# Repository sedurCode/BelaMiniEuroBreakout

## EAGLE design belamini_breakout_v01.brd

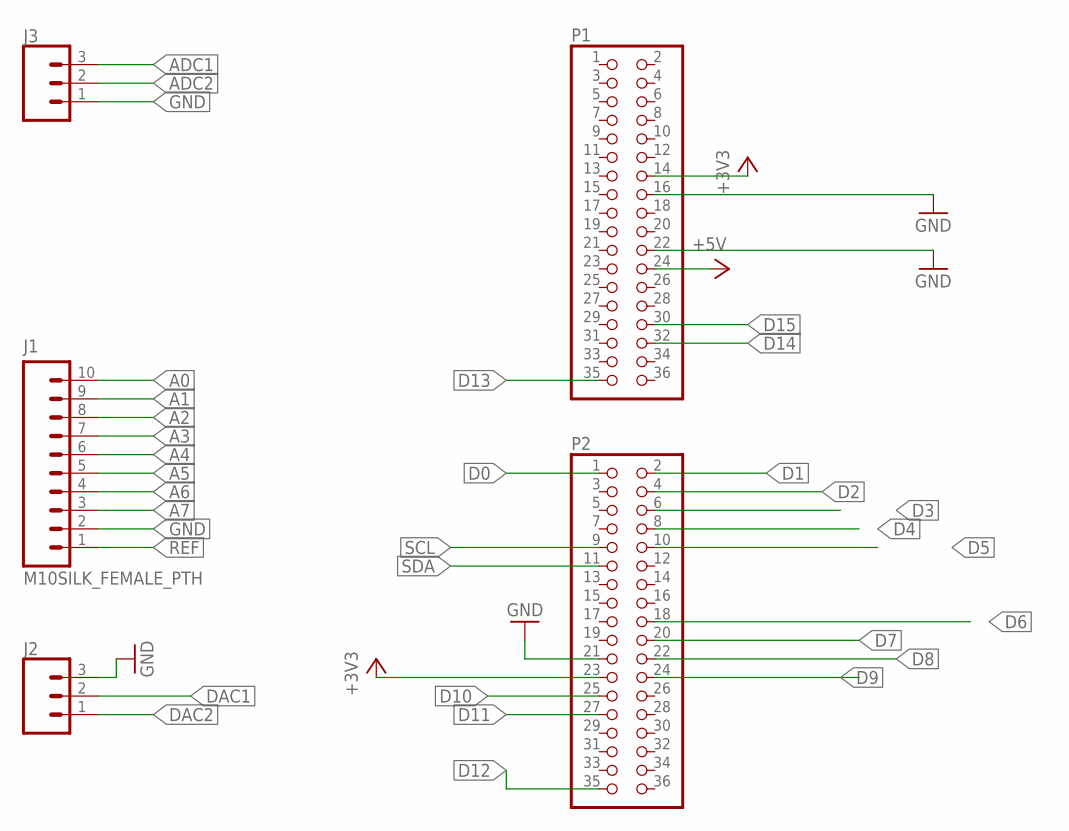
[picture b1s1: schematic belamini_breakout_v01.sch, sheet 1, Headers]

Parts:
J1: M10SILK_FEMALE_PTH; 1X10
J2, J3: CONN_03; 1X03
P1, P2: PINHD-2X18; 2X18

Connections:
+3V3: P1.14, P2.23; also elsewhere on the board
+5V: P1.24; also elsewhere on the board
A0: J1.10; also elsewhere on the board
A1: J1.9; also elsewhere on the board
A2: J1.8; also elsewhere on the board
A3: J1.7; also elsewhere on the board
A4: J1.6
A5: J1.5
A6: J1.4
A7: J1.3
ADC1: J3.3; also elsewhere on the board
ADC2: J3.2; also elsewhere on the board
D0: P2.1; also elsewhere on the board
D1: P2.2; also elsewhere on the board
D2: P2.4; also elsewhere on the board
D3: P2.6; also elsewhere on the board
D4: P2.8; also elsewhere on the board
D5: P2.10; also elsewhere on the board
D6: P2.18; also elsewhere on the board
D7: P2.20; also elsewhere on the board
D8: P2.22; also elsewhere on the board
D9: P2.24; also elsewhere on the board
D10: P2.25; also elsewhere on the board
D11: P2.27; also elsewhere on the board
D12: P2.35
D13: P1.35; also elsewhere on the board
D14: P1.32; also elsewhere on the board
D15: P1.30; also elsewhere on the board
DAC1: J2.2; also elsewhere on the board
DAC2: J2.1; also elsewhere on the board
GND: J1.2, J2.3, J3.1, P1.16, P1.22, P2.21; also elsewhere on the board
REF: J1.1
SCL: P2.9
SDA: P2.11

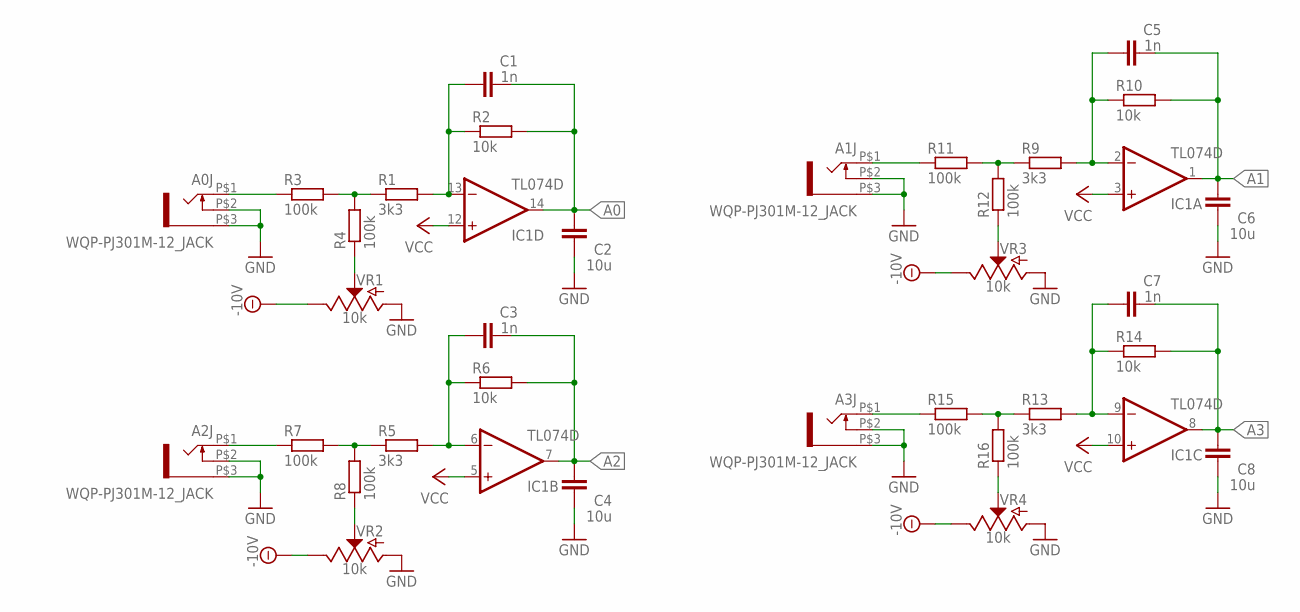
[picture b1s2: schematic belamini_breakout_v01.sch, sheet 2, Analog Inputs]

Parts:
A0J, A1J, A2J, A3J: WQP-PJ301M-12_JACK
C1, C3, C5, C7: 1n; C0603
C2, C4, C6, C8: 10u; C0603
IC1: TL074D; SO14
R1, R5, R9, R13: 3k3; R0603
R2, R6, R10, R14: 10k; R0603
R3, R4, R7, R8, R11, R12, R15, R16: 100k; R0603
VR1, VR2, VR3, VR4: 10k; POT-PTH-ALPS-KIT

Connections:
-10V: VR1.P$1 (E), VR2.P$1 (E), VR3.P$1 (E), VR4.P$1 (E); also elsewhere on the board
A0: C1.2, C2.2, IC1.14 (OUT), R2.2; also elsewhere on the board
A1: C5.2, C6.2, IC1.1 (OUT), R10.2; also elsewhere on the board
A2: C3.2, C4.2, IC1.7 (OUT), R6.2; also elsewhere on the board
A3: C7.2, C8.2, IC1.8 (OUT), R14.2; also elsewhere on the board
GND: A0J.P$2 (3), A0J.P$3 (1), A1J.P$2 (3), A1J.P$3 (1), A2J.P$2 (3), A2J.P$3 (1), A3J.P$2 (3), A3J.P$3 (1), C2.1, C4.1, C6.1, C8.1, VR1.P$3 (A), VR2.P$3 (A), VR3.P$3 (A), VR4.P$3 (A); also elsewhere on the board
unnamed: A0J.P$1 (2), R3.1
unnamed: C1.1, IC1.13 (-IN), R1.2, R2.1
unnamed: R1.1, R3.2, R4.2
unnamed: R4.1, VR1.P$2 (S)
unnamed: C3.1, IC1.6 (-IN), R5.2, R6.1
unnamed: R5.1, R7.2, R8.2
unnamed: A2J.P$1 (2), R7.1
unnamed: R8.1, VR2.P$2 (S)
unnamed: C5.1, IC1.2 (-IN), R9.2, R10.1
unnamed: R9.1, R11.2, R12.2
unnamed: A1J.P$1 (2), R11.1
unnamed: R12.1, VR3.P$2 (S)
unnamed: C7.1, IC1.9 (-IN), R13.2, R14.1
unnamed: R13.1, R15.2, R16.2
unnamed: A3J.P$1 (2), R15.1
unnamed: R16.1, VR4.P$2 (S)
VCC: IC1.3 (+IN), IC1.5 (+IN), IC1.10 (+IN), IC1.12 (+IN); also elsewhere on the board

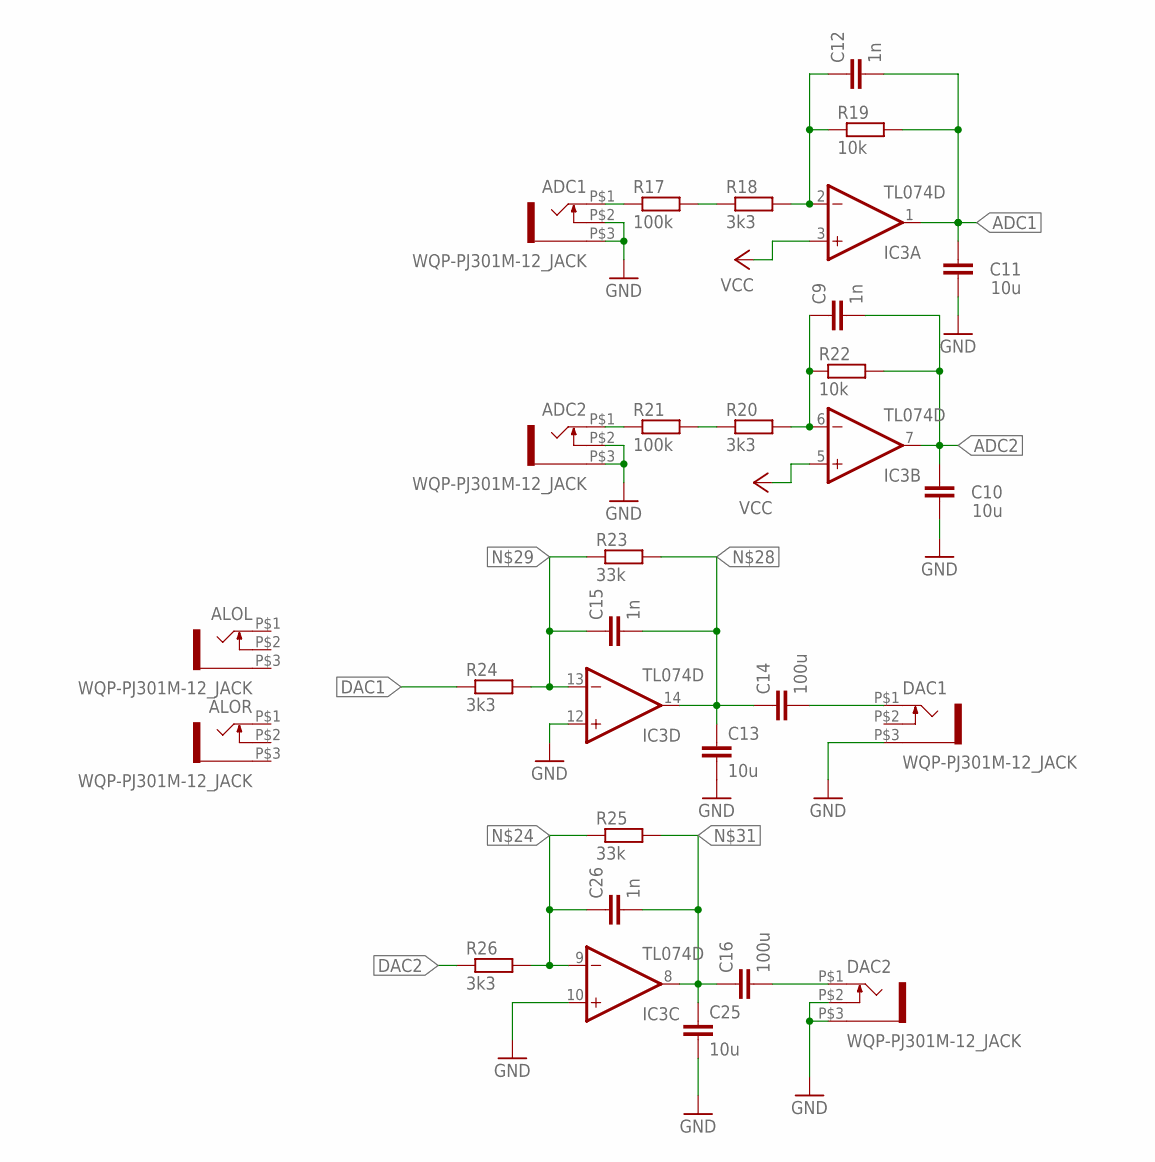
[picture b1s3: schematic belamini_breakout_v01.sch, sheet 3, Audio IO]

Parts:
ADC1, ADC2: WQP-PJ301M-12_JACK
ALOL: WQP-PJ301M-12_JACK
ALOR: WQP-PJ301M-12_JACK
C9, C12, C15, C26: 1n; C0603
C10, C11, C13, C25: 10u; C0603
C14, C16: 100u; C0603
DAC1, DAC2: WQP-PJ301M-12_JACK
IC3: TL074D; SO14
R17, R21: 100k; R0603
R18, R20, R24, R26: 3k3; R0603
R19, R22: 10k; R0603
R23, R25: 33k; R0603

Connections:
ADC1: C11.2, C12.2, IC3.1 (OUT), R19.2; also elsewhere on the board
ADC2: C9.2, C10.2, IC3.7 (OUT), R22.2; also elsewhere on the board
DAC1: R24.1; also elsewhere on the board
DAC2: R26.1; also elsewhere on the board
GND: ADC1.P$2 (3), ADC1.P$3 (1), ADC2.P$2 (3), ADC2.P$3 (1), C10.1, C11.1, C13.2, C25.2, DAC1.P$3 (1), DAC2.P$2 (3), DAC2.P$3 (1), IC3.10 (+IN), IC3.12 (+IN); also elsewhere on the board
unnamed: ADC1.P$1 (2), R17.1
unnamed: R17.2, R18.1
unnamed: C12.1, IC3.2 (-IN), R18.2, R19.1
unnamed: C9.1, IC3.6 (-IN), R20.2, R22.1
unnamed: C26.1, IC3.9 (-IN), R25.1, R26.2
unnamed: R20.1, R21.2
unnamed: ADC2.P$1 (2), R21.1
unnamed: C14.2, DAC1.P$1 (2)
unnamed: C13.1, C14.1, C15.2, IC3.14 (OUT), R23.2
unnamed: C15.1, IC3.13 (-IN), R23.1, R24.2
unnamed: C16.1, C25.1, C26.2, IC3.8 (OUT), R25.2
unnamed: C16.2, DAC2.P$1 (2)
VCC: IC3.3 (+IN), IC3.5 (+IN); also elsewhere on the board

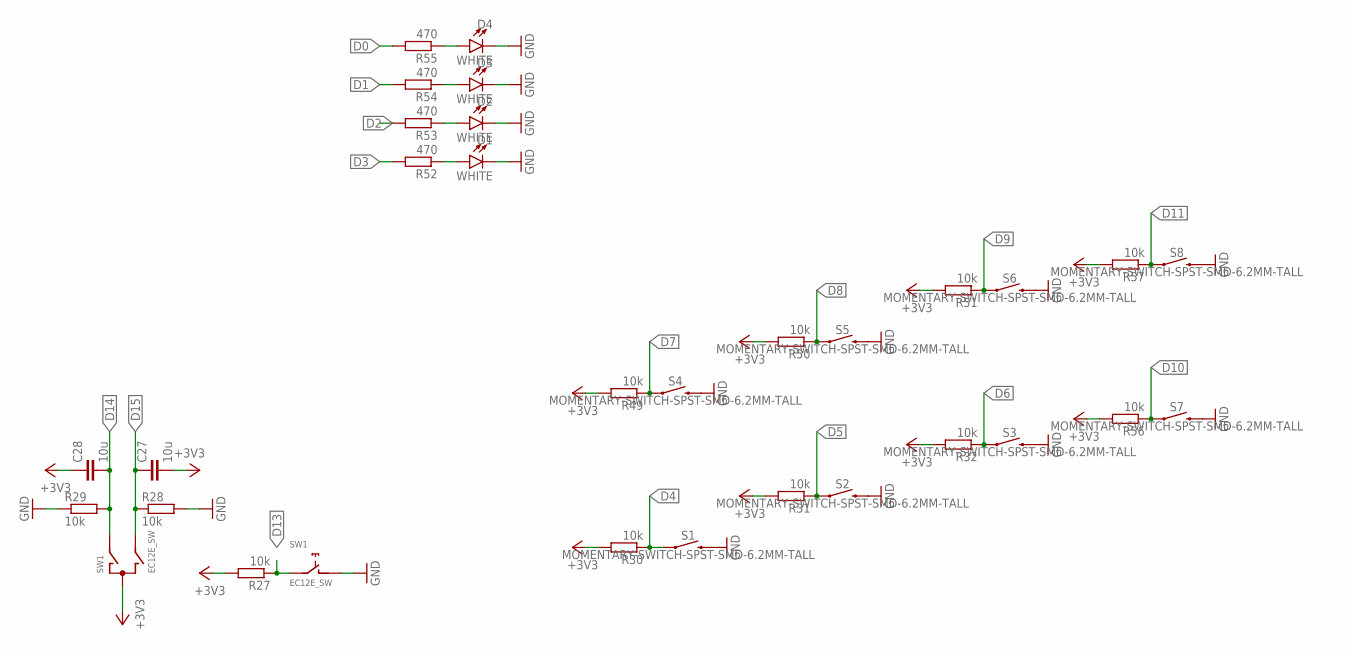
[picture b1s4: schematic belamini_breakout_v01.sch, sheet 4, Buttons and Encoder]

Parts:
C27, C28: 10u; C0603
D1, D2, D3, D4: WHITE; LED-1206
R27, R28, R29, R30, R31, R32, R49, R50, R51, R56, R57: 10k; R0603
R52, R53, R54, R55: 470; R0603
S1, S2, S3, S4, S5, S6, S7, S8: MOMENTARY-SWITCH-SPST-SMD-6.2MM-TALL; TACTILE_SWITCH_SMD_6.2MM_TALL
SW1: EC12E_SW; ALPS_EC12E_SW

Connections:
+3V3: C27.2, C28.1, R27.2, R30.2, R31.2, R32.2, R49.2, R50.2, R51.2, R56.2, R57.2, SW1.C; also elsewhere on the board
D0: R55.2; also elsewhere on the board
D1: R54.2; also elsewhere on the board
D2: R53.2; also elsewhere on the board
D3: R52.2; also elsewhere on the board
D4: R30.1, S1.A2 (1); also elsewhere on the board
D5: R31.1, S2.A2 (1); also elsewhere on the board
D6: R32.1, S3.A2 (1); also elsewhere on the board
D7: R49.1, S4.A2 (1); also elsewhere on the board
D8: R50.1, S5.A2 (1); also elsewhere on the board
D9: R51.1, S6.A2 (1); also elsewhere on the board
D10: R56.1, S7.A2 (1); also elsewhere on the board
D11: R57.1, S8.A2 (1); also elsewhere on the board
D13: R27.1, SW1.E (2); also elsewhere on the board
D14: C28.2, R29.2, SW1.A; also elsewhere on the board
D15: C27.1, R28.1, SW1.B; also elsewhere on the board
GND: D1.C, D2.C, D3.C, D4.C, R28.2, R29.1, S1.B2 (2), S2.B2 (2), S3.B2 (2), S4.B2 (2), S5.B2 (2), S6.B2 (2), S7.B2 (2), S8.B2 (2), SW1.D (1); also elsewhere on the board
unnamed: D4.A, R55.1
unnamed: D3.A, R54.1
unnamed: D2.A, R53.1
unnamed: D1.A, R52.1

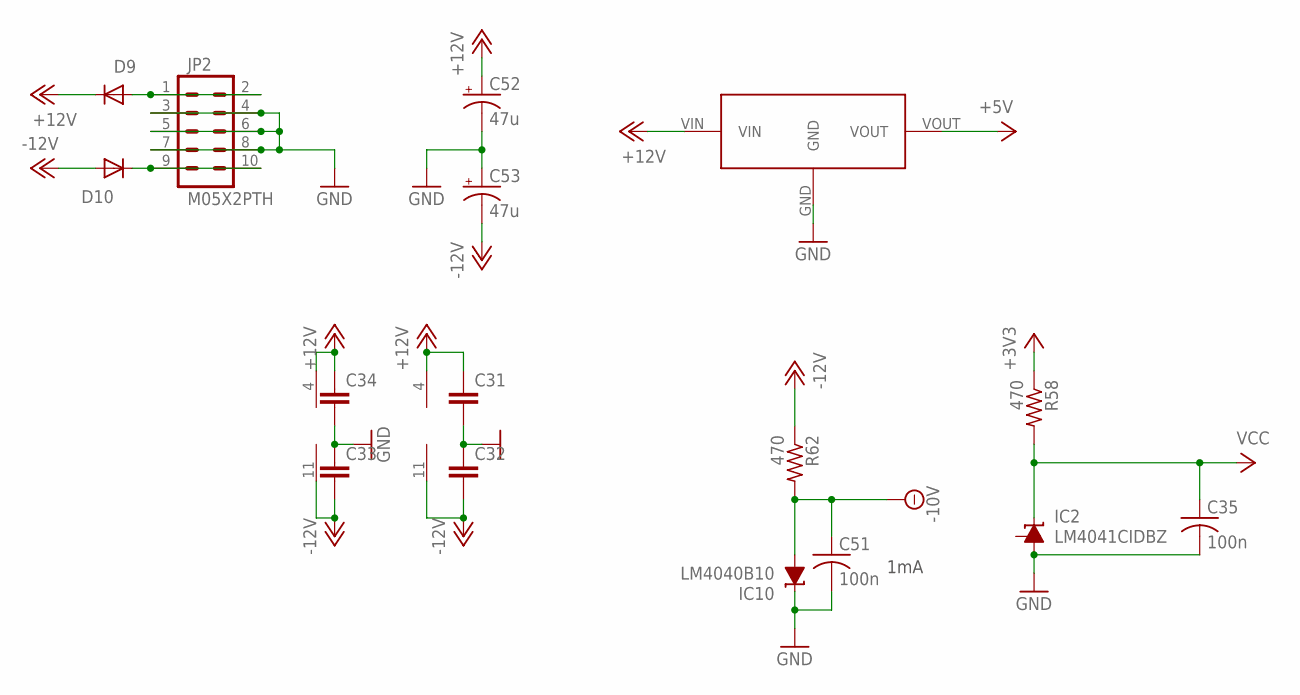
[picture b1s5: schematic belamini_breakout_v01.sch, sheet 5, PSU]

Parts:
C31, C32, C33, C34: C-EUC0603; C0603
C35, C51: 100n; C0603
C52, C53: 47u; PANASONIC_D
D9, D10: 1N5819HW; SOD123
IC1, IC3: TL074D; SO14
IC2: LM4041CIDBZ; DBZ_R-PDSO-G3
IC10: LM4040B10; DBZ_R-PDSO-G3
JP2: M05X2PTH; AVR_ICSP
R58, R62: 470; R0603
U$1: RECOM785.0; R-78XX-1.0

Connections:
+3V3: R58.1; also elsewhere on the board
+5V: U$1.VOUT; also elsewhere on the board
+12V: C31.1, C34.1, C52.+, D9.C, IC1.4 (V+), IC3.4 (V+), U$1.VIN
-10V: C51.1, IC10.2 (A), R62.2; also elsewhere on the board
-12V: C32.2, C33.2, C53.-, D10.A, IC1.11 (V-), IC3.11 (V-), R62.1
GND: C31.2, C32.1, C33.1, C34.2, C35.2, C51.2, C52.-, C53.+, IC2.3 (A), IC10.1 (C), JP2.3, JP2.4, JP2.5, JP2.6, JP2.7, JP2.8, U$1.GND; also elsewhere on the board
unnamed: D9.A, JP2.1, JP2.2
unnamed: D10.C, JP2.9, JP2.10
VCC: C35.1, IC2.2 (C), R58.2; also elsewhere on the board

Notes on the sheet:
1mA

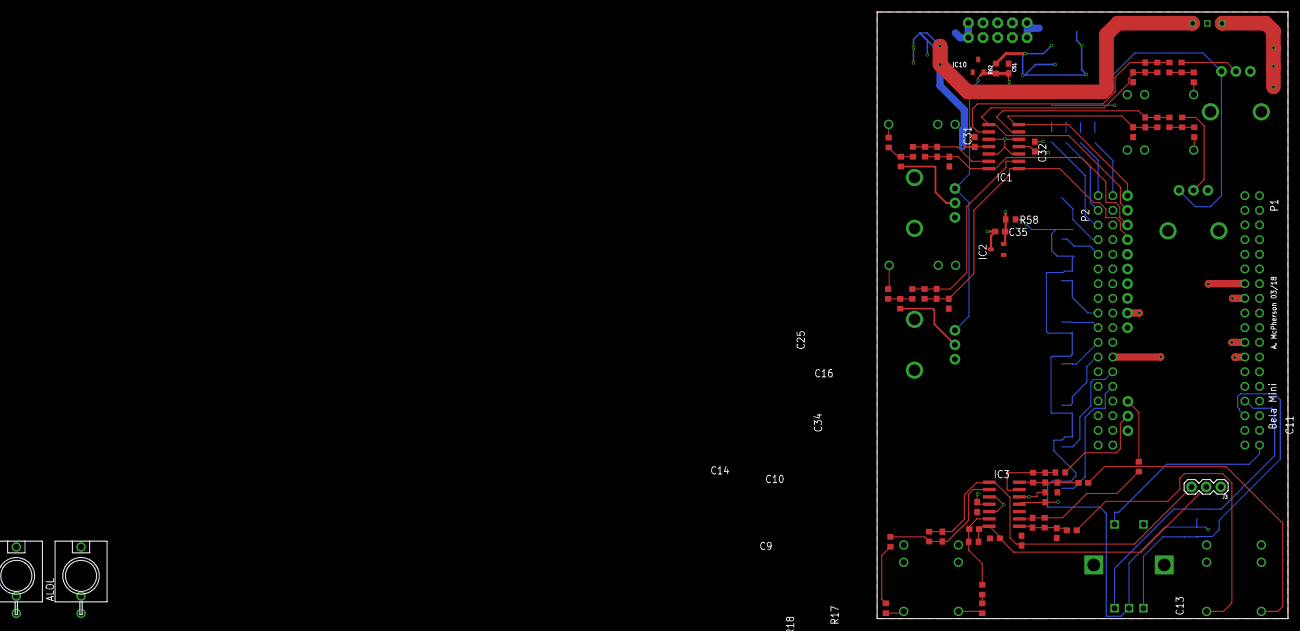
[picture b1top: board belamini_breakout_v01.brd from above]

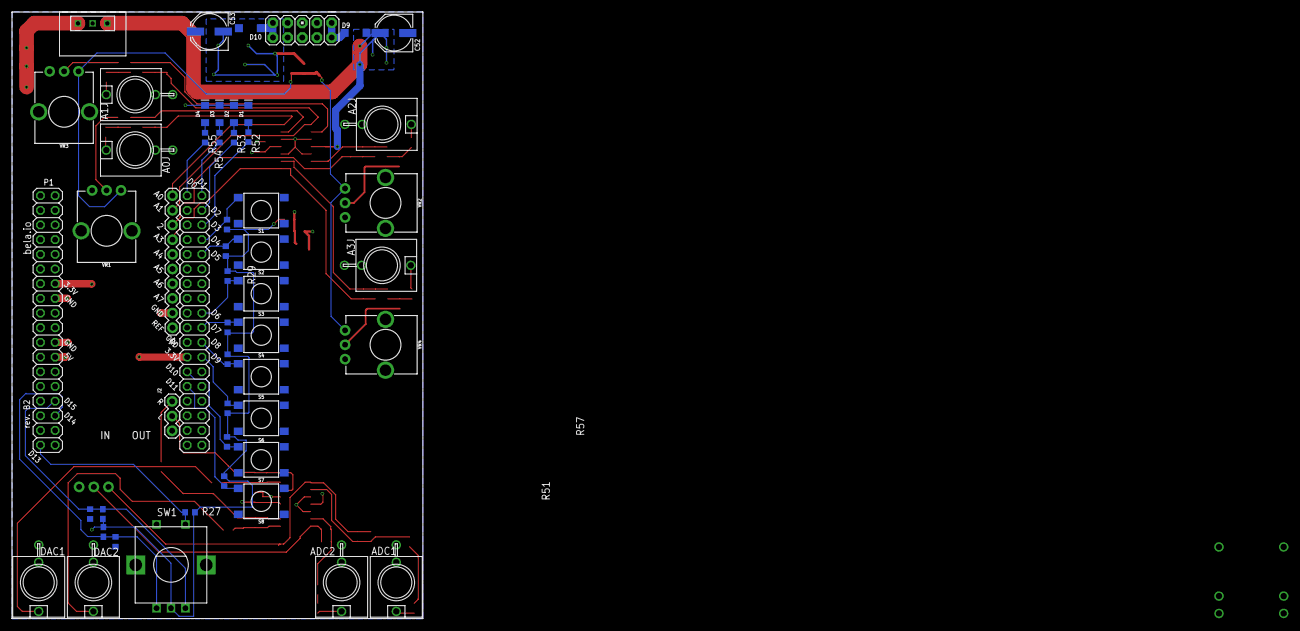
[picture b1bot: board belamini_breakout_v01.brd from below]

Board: 4 copper layers, 71.1 x 105.0 mm, 111 parts (52 on the bottom side), 64 nets.

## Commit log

2019-03-30 begun design, with prototype scaling circuit
2019-04-01 schematic components and layout
2019-04-01 minimise features and layout
2019-04-01 gorund plane front and back and make 4 layer
2019-04-01 clear out all DRV (except priority)
2019-04-01 Swap output to line out

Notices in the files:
parts and their libraries:
SparkFun-Connectors: Licensing: CC v3.0 Share-Alike You are welcome to use this library for commercial purposes.
SparkFun-Connectors: Licensing: Creative Commons ShareAlike 4.0 International - https://creativecommons.org/licenses/by-sa/4.0
